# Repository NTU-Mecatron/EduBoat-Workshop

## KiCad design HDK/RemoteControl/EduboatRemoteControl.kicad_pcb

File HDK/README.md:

# HDK

Stay tuned! Hardware resources will be ported over soon!

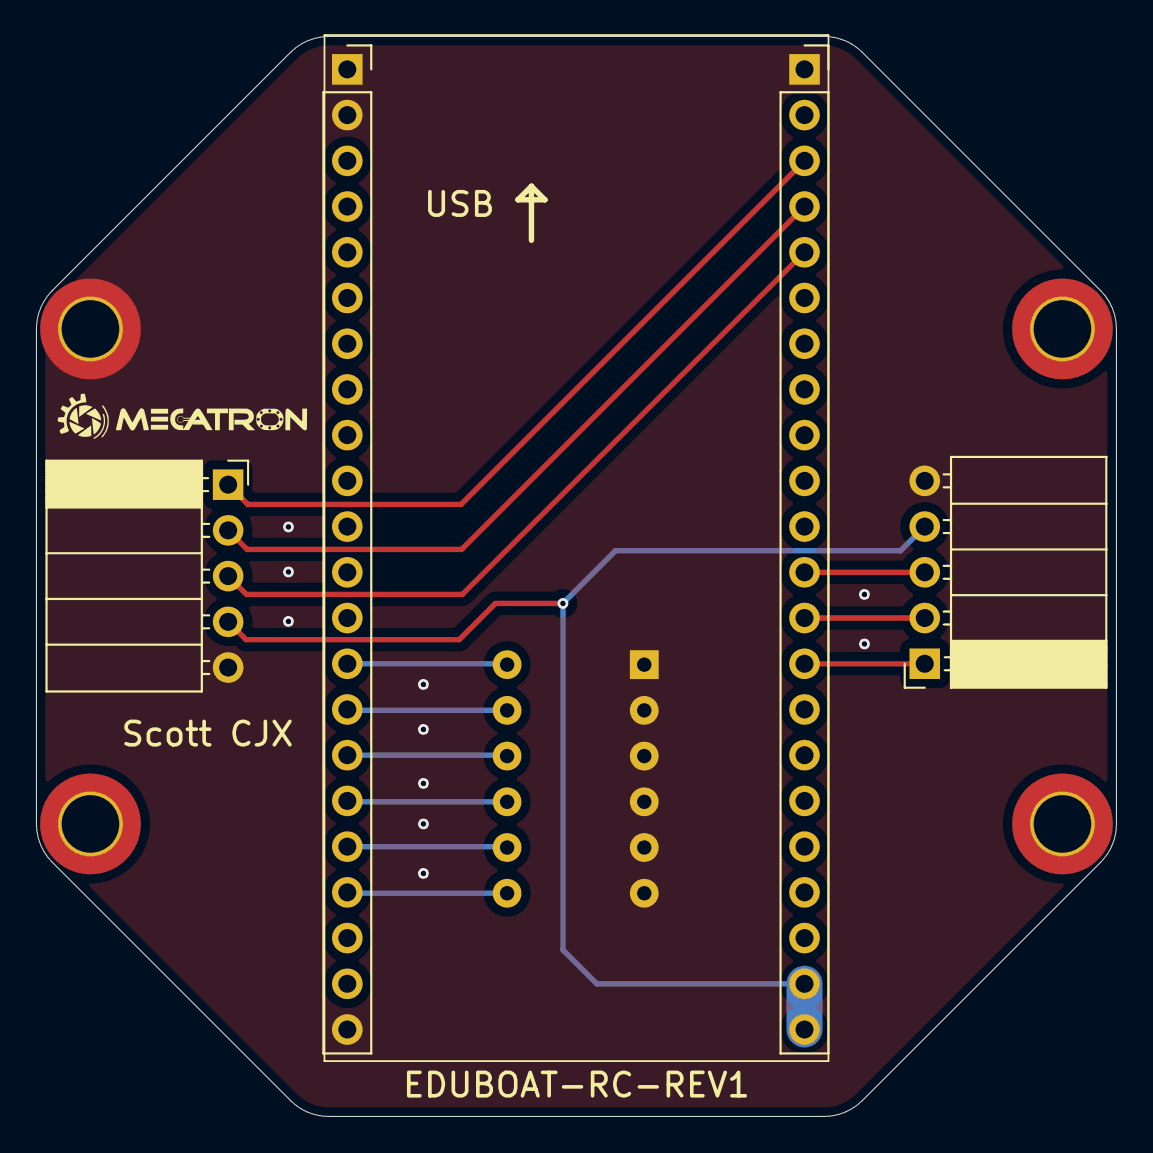
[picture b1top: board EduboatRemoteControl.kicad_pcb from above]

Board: 2 copper layers, 60.0 x 60.0 mm, 9 parts (1 on the bottom side), 14 nets.

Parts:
H101, H102, H103, H104: MountingHole_Pad; MountingHole_3.2mm_M3_DIN965_Pad_TopBottom
J101: ESP32-L; PinSocket_1x22_P2.54mm_Vertical
J102: ESP32-R; PinSocket_1x22_P2.54mm_Vertical
J103, J104: Conn_01x05; PinSocket_1x05_P2.54mm_Horizontal
SW101: SW_DIP_x06; SW_DIP_SPSTx06_Slide_9.78x17.42mm_W7.62mm_P2.54mm

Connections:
+3V3: J102.21, J102.22, J103.4, J104.4
/CHNL-SEL-B0: J101.14, SW101.12
/CHNL-SEL-B1: J101.15, SW101.11
/CHNL-SEL-B2: J101.16, SW101.10
/CHNL-SEL-B3: J101.17, SW101.9
/CHNL-SEL-B4: J101.18, SW101.8
/CHNL-SEL-B5: J101.19, SW101.7
/GP12: J102.5, J103.3
/GP13: J102.4, J103.2
/GP14: J102.3, J103.1
/GP16: J102.14, J104.1
/GP17: J102.13, J104.2
/GP18: J102.12, J104.3
GND: H101.1, J101.1, J101.2, J101.22, J102.1, J103.5, J104.5, SW101.1, SW101.2, SW101.3, SW101.4, SW101.5, SW101.6

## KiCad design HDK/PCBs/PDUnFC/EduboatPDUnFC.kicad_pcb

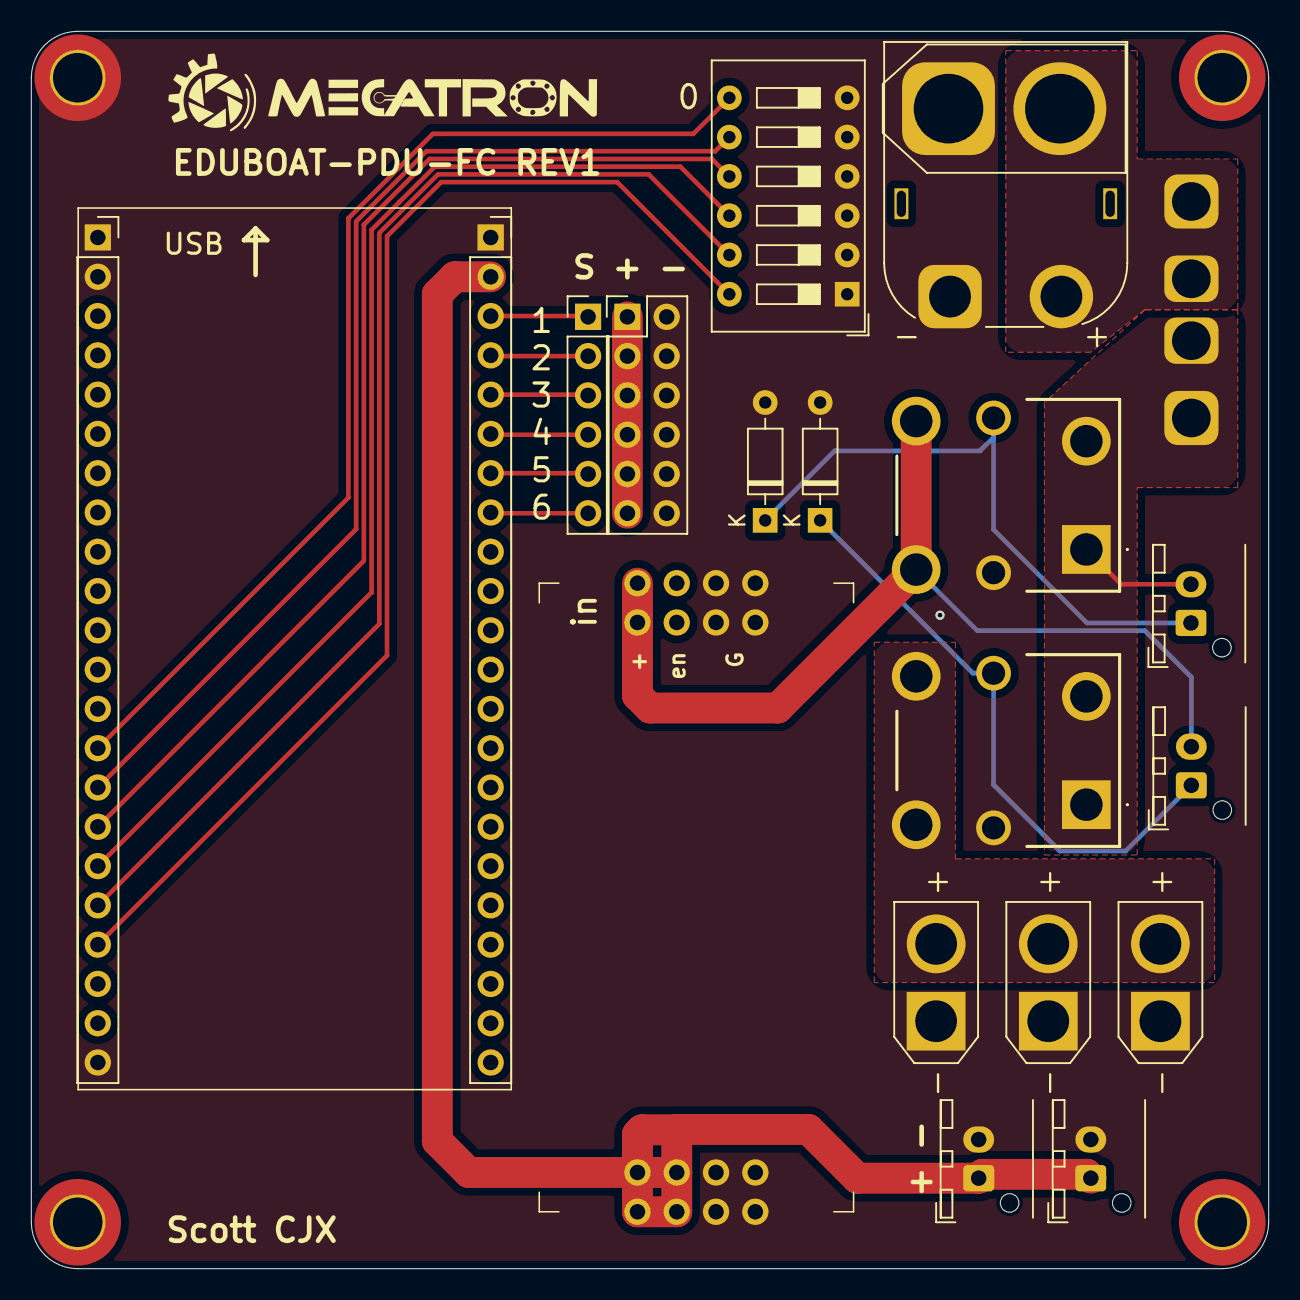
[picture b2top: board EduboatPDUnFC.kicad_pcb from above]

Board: 2 copper layers, 80.0 x 80.0 mm, 24 parts (0 on the bottom side), 22 nets.

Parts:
D101, D102: D; D_DO-35_SOD27_P7.62mm_Horizontal
F101: Fuse; FUSE-MCCQ-121
H101, H102, H103, H104: MountingHole_Pad; MountingHole_3.2mm_M3_DIN965_Pad_TopBottom
J101: ESP32-L; PinSocket_1x22_P2.54mm_Vertical
J102: ESP32-R; PinSocket_1x22_P2.54mm_Vertical
J103: Batt; AMASS_XT60PW-M_1x02_P7.20mm_Horizontal
J104, J107, J110, J113: Conn_PWR; JST_XH_B2B-XH-AM_1x02_P2.50mm_Vertical
J105, J106, J108: Conn_PWR; AMASS_XT30U-M_1x02_P5.0mm_Vertical
J109: Batt; AMASS_XT60-M_1x02_P7.20mm_Vertical
J111: PWM; PinHeader_1x06_P2.54mm_Vertical
J112: PWM; PinHeader_2x06_P2.54mm_Vertical
K101, K102: Relay_SPST-NO; G8PM1AW7RDC12
SW101: SW_DIP_x06; SW_DIP_SPSTx06_Slide_9.78x17.42mm_W7.62mm_P2.54mm
U101: TPS5460 康威科技

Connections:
+3V3: J102.21, J102.22
+5V: J102.2, J110.+ (Pin_1), J113.+ (Pin_1), U101.2 (V_{OUT})
+BATT: F101.1, J103.+ (Pin_1), J109.+ (Pin_1)
/CHNL-SEL-B0: J101.14, SW101.7
/CHNL-SEL-B1: J101.15, SW101.8
/CHNL-SEL-B2: J101.16, SW101.9
/CHNL-SEL-B3: J101.17, SW101.10
/CHNL-SEL-B4: J101.18, SW101.11
/CHNL-SEL-B5: J101.19, SW101.12
/PWM-01: J102.3, J111.1
/PWM-02: J102.4, J111.2
/PWM-03: J102.5, J111.3
/PWM-04: J102.6, J111.4
/PWM-05: J102.7, J111.5
/PWM-06: J102.8, J111.6
GND: D101.2 (A), D102.2 (A), H101.1, J101.1, J101.2, J101.22, J102.1, J103.- (Pin_2), J105.- (Pin_2), J106.- (Pin_2), J108.- (Pin_2), J109.- (Pin_2), J110.- (Pin_2), J112.2, J112.4, J112.6, J112.8, J112.10, J112.12, J113.- (Pin_2), K101.A2, K102.A2, SW101.1, SW101.2, SW101.3, SW101.4, SW101.5, SW101.6, U101.G (GND)
unnamed: D101.1 (K), J104.+ (Pin_1), K101.A1
unnamed: D102.1 (K), J107.+ (Pin_1), K102.A1
V_{Fused}: F101.2, J104.- (Pin_2), K101.14, K102.14
V_{HV-BUCK}: J112.1, J112.3, J112.5, J112.7, J112.9, J112.11
V_{HV}: J105.+ (Pin_1), J106.+ (Pin_1), J108.+ (Pin_1), K102.13
V_{LV}: J107.- (Pin_2), K101.13, U101.1 (V_{IN})

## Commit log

2025-05-01 working v1
2025-05-01 added timeout for boat
2025-05-21 update servo offset
2025-05-21 updated dip switch fix
2025-05-21 added esc pwm tester
2025-05-21 updated code
2025-08-02 refactored
2025-08-02 updated docs
2025-08-02 updated sw
2025-08-02 added HDK
2025-08-03 updated docs & refactored
2025-08-03 added pio compile
2025-08-03 fixed name
